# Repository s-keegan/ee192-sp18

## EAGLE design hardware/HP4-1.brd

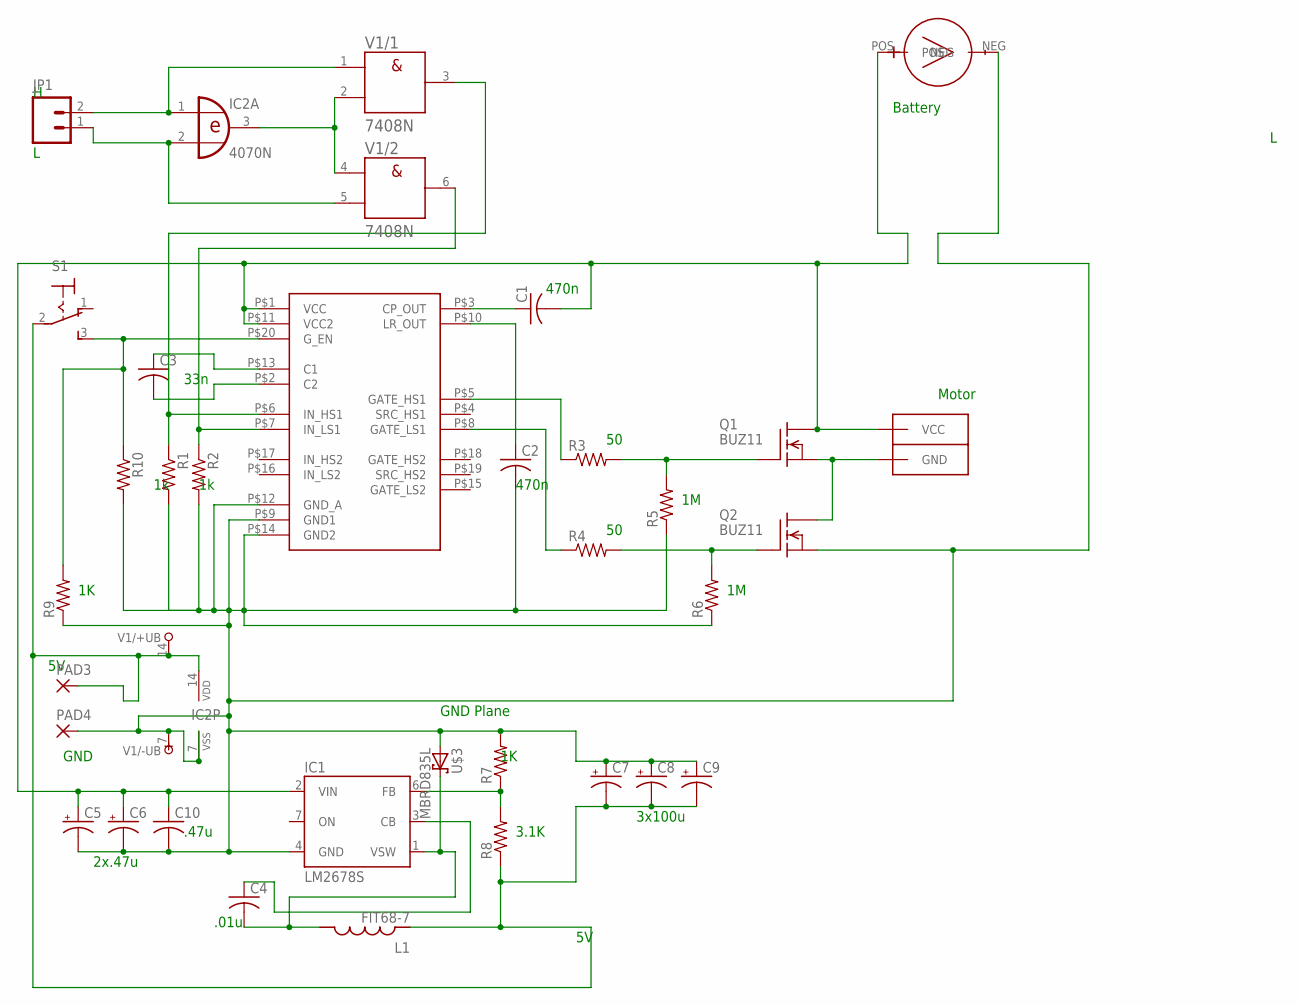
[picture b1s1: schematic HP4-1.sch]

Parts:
C1, C2, C3, C10: C-USC1206; C1206
C4: C-US025-024X044; C025-024X044
C5, C6, C7, C8, C9: CPOL-USCT6032; CT6032
IC1: LM2678S; TO263-7
IC2: 4070N; DIL14
JP1: M02PTH; 1X02
L1: FIT68-7
MOTOR: ANDERSON_PP_DOUBLEHORIZONTAL; ANDERSON_PP_DOUB_HORZ
PAD3, PAD4: 3,17/1,3
Q1, Q2: BUZ11; TO220
R1, R2, R3, R4, R5, R6, R10: R-US_M1206; M1206
R7, R8, R9: R-US_R1206; R1206
S1: 320-916
U$1: MC33883DIL20_600MIL_CARRIER; DIL20_600MIL
U$3: MBRD835L; DPAK
U$4: BATT
V1: 7408N; DIL14

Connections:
GND: C2.2, C5.-, C6.-, C7.+, C8.+, C9.+, C10.2, IC1.4 (GND), IC2.7 (VSS), PAD4.1, Q2.3 (S), R1.2, R2.2, R5.1, R6.1, R7.2, R9.1, R10.2, U$1.P$9 (GND1), U$1.P$12 (GND_A), U$1.P$14 (GND2), U$3.P$1 (A), U$3.P$2 (A), U$4.NEG, V1.7 (-UB)
unnamed: R1.1, U$1.P$6 (IN_HS1), V1.3 (Y)
unnamed: R2.1, U$1.P$7 (IN_LS1), V1.6 (Y)
unnamed: Q1.1 (G), R3.2, R5.2
unnamed: C1.1, U$1.P$3 (CP_OUT)
unnamed: Q2.1 (G), R4.2, R6.2
unnamed: C1.2, C5.+, C6.+, C10.1, IC1.2 (VIN), MOTOR.PIN2 (VCC), MOTOR.PIN2-LEAD (VCC), Q1.2 (D), U$1.P$1 (VCC), U$1.P$11 (VCC2), U$4.POS
unnamed: MOTOR.PIN1 (GND), MOTOR.PIN1-LEAD (GND), Q1.3 (S), Q2.2 (D)
unnamed: IC1.6 (FB), R7.1, R8.2
unnamed: R3.1, U$1.P$5 (GATE_HS1)
unnamed: R4.1, U$1.P$8 (GATE_LS1)
unnamed: C2.1, U$1.P$10 (LR_OUT)
unnamed: C7.-, C8.-, C9.-, IC2.14 (VDD), L1.P$1, PAD3.1, R8.1, S1.2, V1.14 (+UB)
unnamed: C3.1, U$1.P$13 (C1)
unnamed: C3.2, U$1.P$2 (C2)
unnamed: IC2.1 (I0), JP1.2, V1.1 (A)
unnamed: C4.1, IC1.3 (CB)
unnamed: C4.2, IC1.1 (VSW), L1.P$2, U$3.P$3 (C)
unnamed: R9.2, R10.1, S1.3 (S), U$1.P$20 (G_EN)
unnamed: IC2.2 (I1), JP1.1, V1.5 (B)
unnamed: IC2.3 (O), V1.2 (B), V1.4 (A)

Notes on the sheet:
Battery
Motor
470n
GND Plane
33n
3.1K
.01u
3x100u
2x.47u
.47u
GND

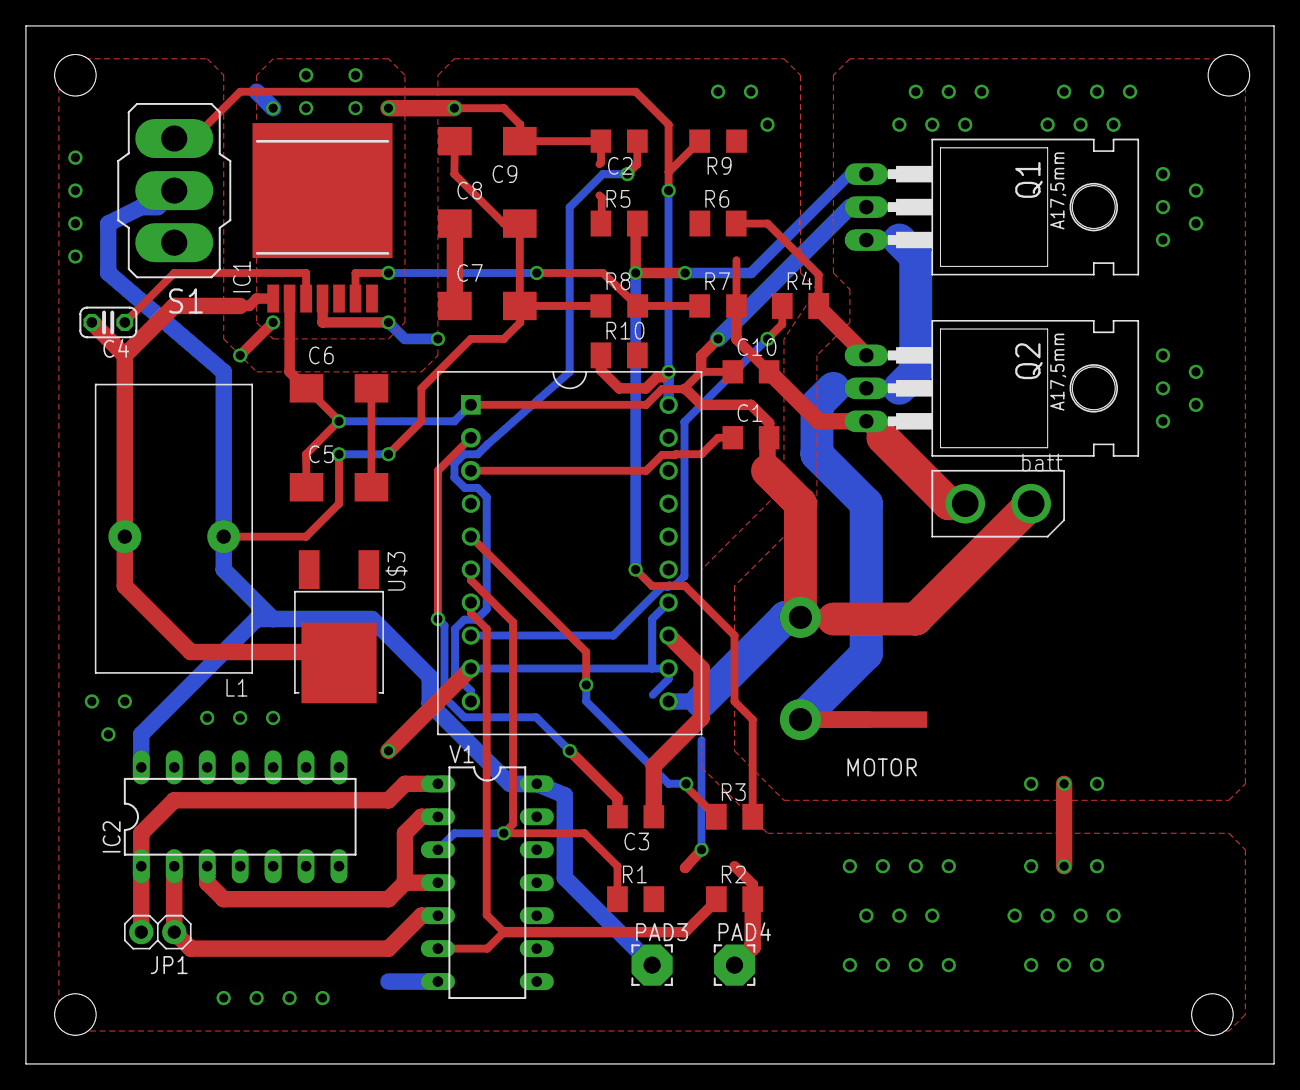
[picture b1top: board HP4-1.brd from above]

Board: 2 copper layers, 96.2 x 80.0 mm, 34 parts (0 on the bottom side), 21 nets.

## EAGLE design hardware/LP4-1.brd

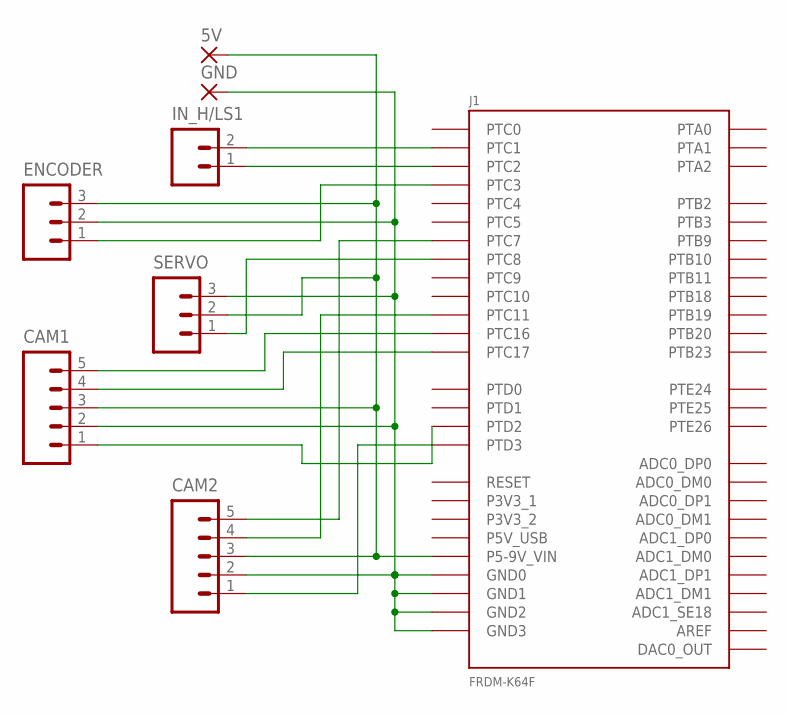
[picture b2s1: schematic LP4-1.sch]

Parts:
5V: 3,17/1,3
CAM1, CAM2: M05PTH; 1X05
ENCODER: M03PTH; 1X03
GND: 3,17/1,3
IN_H/LS1: M02PTH; 1X02
J1: FRDM-K64F
SERVO: M03PTH; 1X03

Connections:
GND: CAM1.2, CAM2.2, ENCODER.2, GND.1, J1.J2-3 (GND0), J1.J2-14 (GND1), J1.J3-12 (GND2), J1.J3-14 (GND3), SERVO.3
unnamed: IN_H/LS1.2, J1.J1-5 (PTC1)
unnamed: IN_H/LS1.1, J1.J1-14 (PTC2)
unnamed: 5V.1, CAM1.3, CAM2.3, ENCODER.3, J1.J3-16 (P5-9V_VIN), SERVO.2
unnamed: ENCODER.1, J1.J1-16 (PTC3)
unnamed: CAM1.1, J1.J2-8 (PTD2)
unnamed: J1.J1-7 (PTC8), SERVO.1
unnamed: CAM1.5, J1.J1-2 (PTC16)
unnamed: CAM1.4, J1.J1-4 (PTC17)
unnamed: CAM2.1, J1.J2-10 (PTD3)
unnamed: CAM2.4, J1.J4-10 (PTC11)
unnamed: CAM2.5, J1.J1-13 (PTC7)

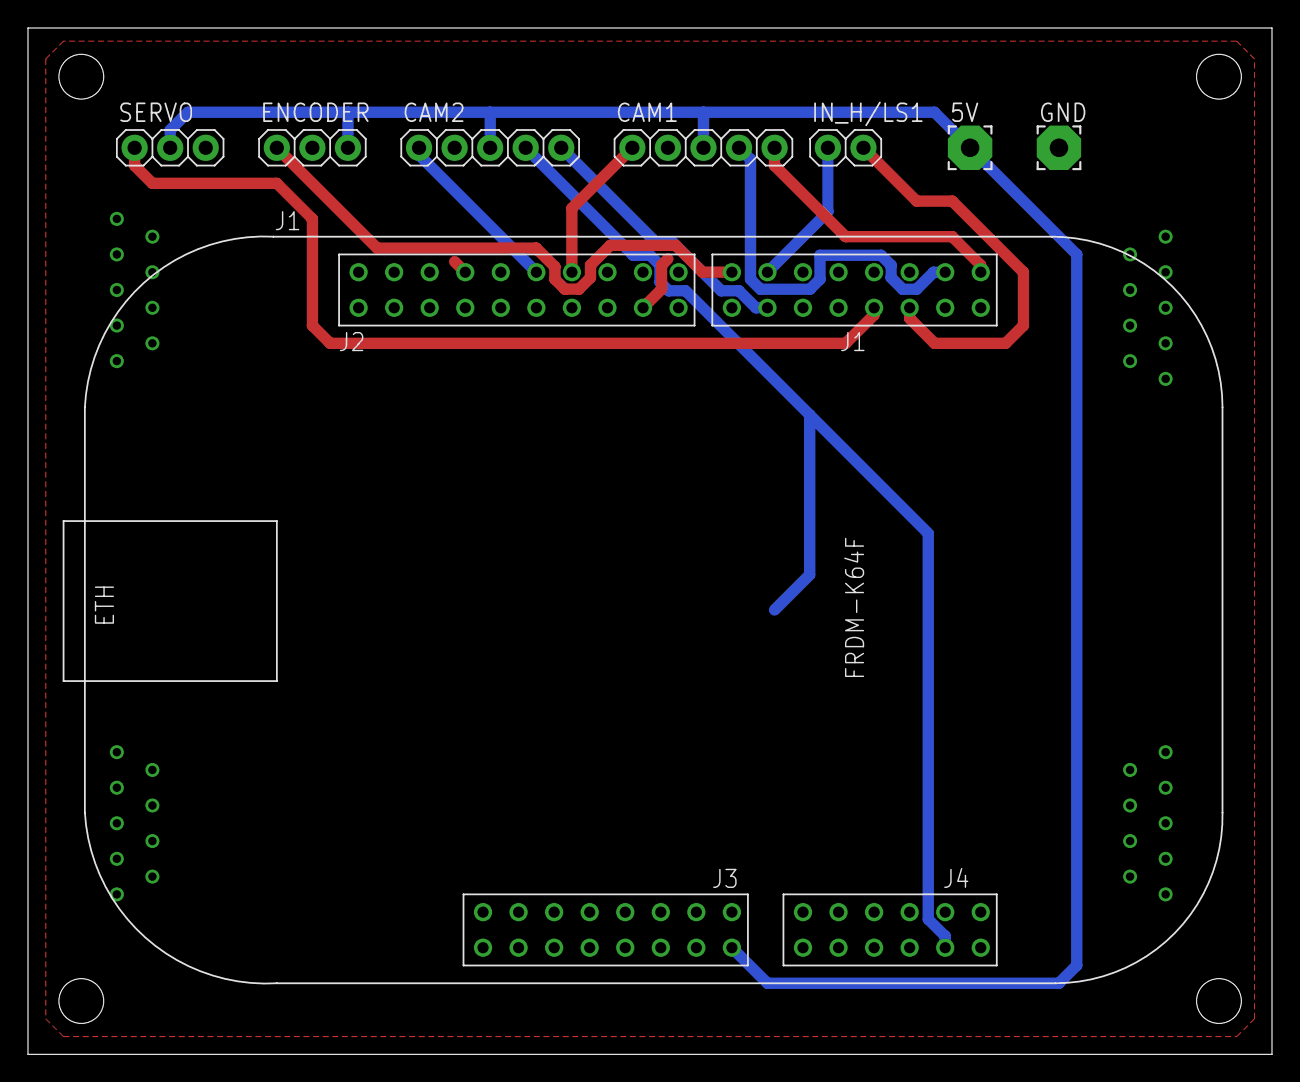
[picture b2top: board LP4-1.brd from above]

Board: 2 copper layers, 88.9 x 73.3 mm, 8 parts (0 on the bottom side), 12 nets.

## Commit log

2018-03-08 initial commit, current boards/schematics and 1st homework
2018-03-08 added sample data for hw1
2018-03-08 updated hw1 to store previous center, fixed errors
